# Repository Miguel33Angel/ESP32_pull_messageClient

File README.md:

# ESP32_pull_messageClient
Arduino program that gets messages from web server and display them in LCD

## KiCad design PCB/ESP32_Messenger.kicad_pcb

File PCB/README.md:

This directory contains the first version of the PCB designed for this project
As such, it may contain errors and it hasn't been fully tested yet

Aditional files of the custom schematics are included in a repository appart:

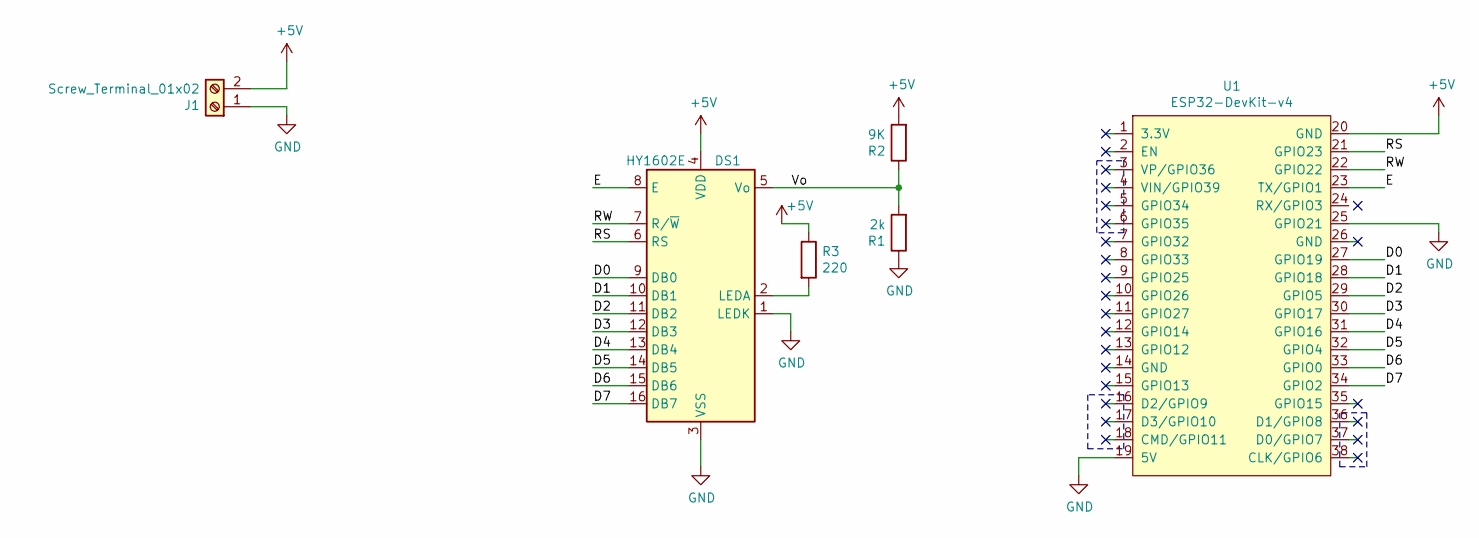
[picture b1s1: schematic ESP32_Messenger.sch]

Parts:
DS1: HY1602E; PinHeader_1x16_P2.54mm_Vertical
J1: Screw_Terminal_01x02; TerminalBlock_TE_282834-2_1x02_P2.54mm_Horizontal
R1: 2k; R_Axial_DIN0207_L6.3mm_D2.5mm_P7.62mm_Horizontal
R2: 9K; R_Axial_DIN0207_L6.3mm_D2.5mm_P7.62mm_Horizontal
R3: 220; R_Axial_DIN0207_L6.3mm_D2.5mm_P7.62mm_Horizontal
U1: ESP32-DevKit-v4; ESP32-Dev-Kit-38

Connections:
+5V: DS1.4 (VDD), J1.2, R2.2, R3.1, U1.20 (GND)
/D0: DS1.9 (DB0), U1.27 (GPIO19)
/D1: DS1.10 (DB1), U1.28 (GPIO18)
/D2: DS1.11 (DB2), U1.29 (GPIO5)
/D3: DS1.12 (DB3), U1.30 (GPIO17)
/D4: DS1.13 (DB4), U1.31 (GPIO16)
/D5: DS1.14 (DB5), U1.32 (GPIO4)
/D6: DS1.15 (DB6), U1.33 (GPIO0)
/D7: DS1.16 (DB7), U1.34 (GPIO2)
/E: DS1.8 (E), U1.23 (TX/GPIO1)
/RS: DS1.6 (RS), U1.21 (GPIO23)
/RW: DS1.7 (R/~W), U1.22 (GPIO22)
/Vo: DS1.5 (Vo), R1.2, R2.1
GND: DS1.1 (LEDK), DS1.3 (VSS), J1.1, R1.1, U1.19 (5V), U1.25 (GPIO21)
unnamed: DS1.2 (LEDA), R3.2

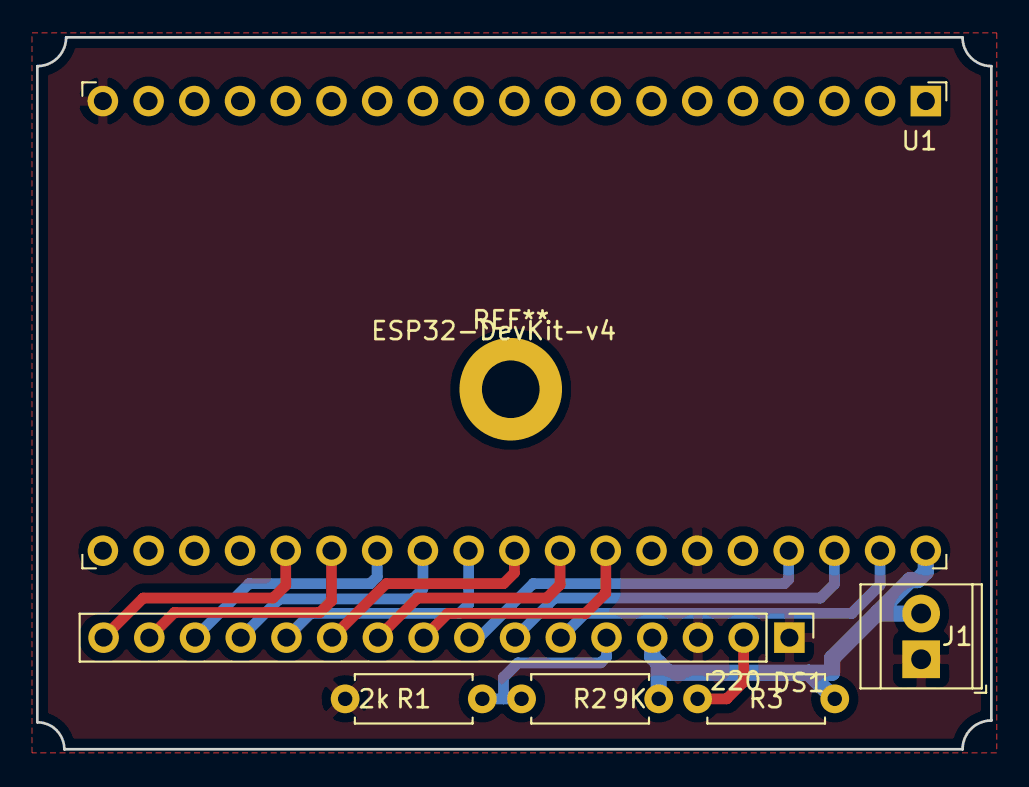
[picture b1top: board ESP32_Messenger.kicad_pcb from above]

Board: 2 copper layers, 53.0 x 39.5 mm, 6 parts (0 on the bottom side), 15 nets.

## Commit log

2021-11-01 First prototype
    Created basic prototype. Only changed needed to make it function is filling: _WIFI_SSID, _WIFI_PSW and _WEB_SERVER_IP
2022-02-08 Removed template header
    Removed text from examples used
